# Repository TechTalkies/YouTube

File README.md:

# 🔧 Tech Talkies YouTube

This repository contains all the Arduino and electronics-related code from my YouTube videos. Each folder corresponds to a separate video or topic, with code examples, wiring tables, and useful documentation.

Support our open source projects:

## 📁 Folder Structure

Each subfolder is named after the video/project and includes:
- Arduino code (`.ino` files)
- Wiring diagrams or connection tables (in Markdown or image format)
- Supporting libraries or references (when applicable)
- A local `README.md` for project-specific details

## 📚 Topics Covered

Some of the topics you'll find here:
- DC motor control using L298N, TB6612FNG, and DRV8833
- Stepper motors with ULN2003 + 28BYJ-48
- Servo motor control with Arduino
- Sensor-based projects (IR, ultrasonic, etc.)
- ESP32 & Wi-Fi-based projects
- More being added regularly...

## 📺 Watch the Videos

Find the full tutorials on my [YouTube channel](https://www.youtube.com/@techtalkies1).

## 🌐 Visit the Website

For additional tutorials, updates, and resources, check out [techtalkies.in](https://techtalkies.in/)

## 🙌 Contribute or Contact

Suggestions or bug reports? Open an issue or drop a comment under the relevant YouTube video.

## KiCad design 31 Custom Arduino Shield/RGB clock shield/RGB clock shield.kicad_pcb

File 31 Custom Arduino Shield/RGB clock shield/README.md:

# Arduino-UNO-R4-Shield-Template
Arduino UNO R4 Shield Template for KiCad 6.<br/>
Based on official Arduino UNO R4 CAD.

## TO DO
- Make better 3D Headers to reflect real measurements.
## Schematic

## PCB View

## 3D View

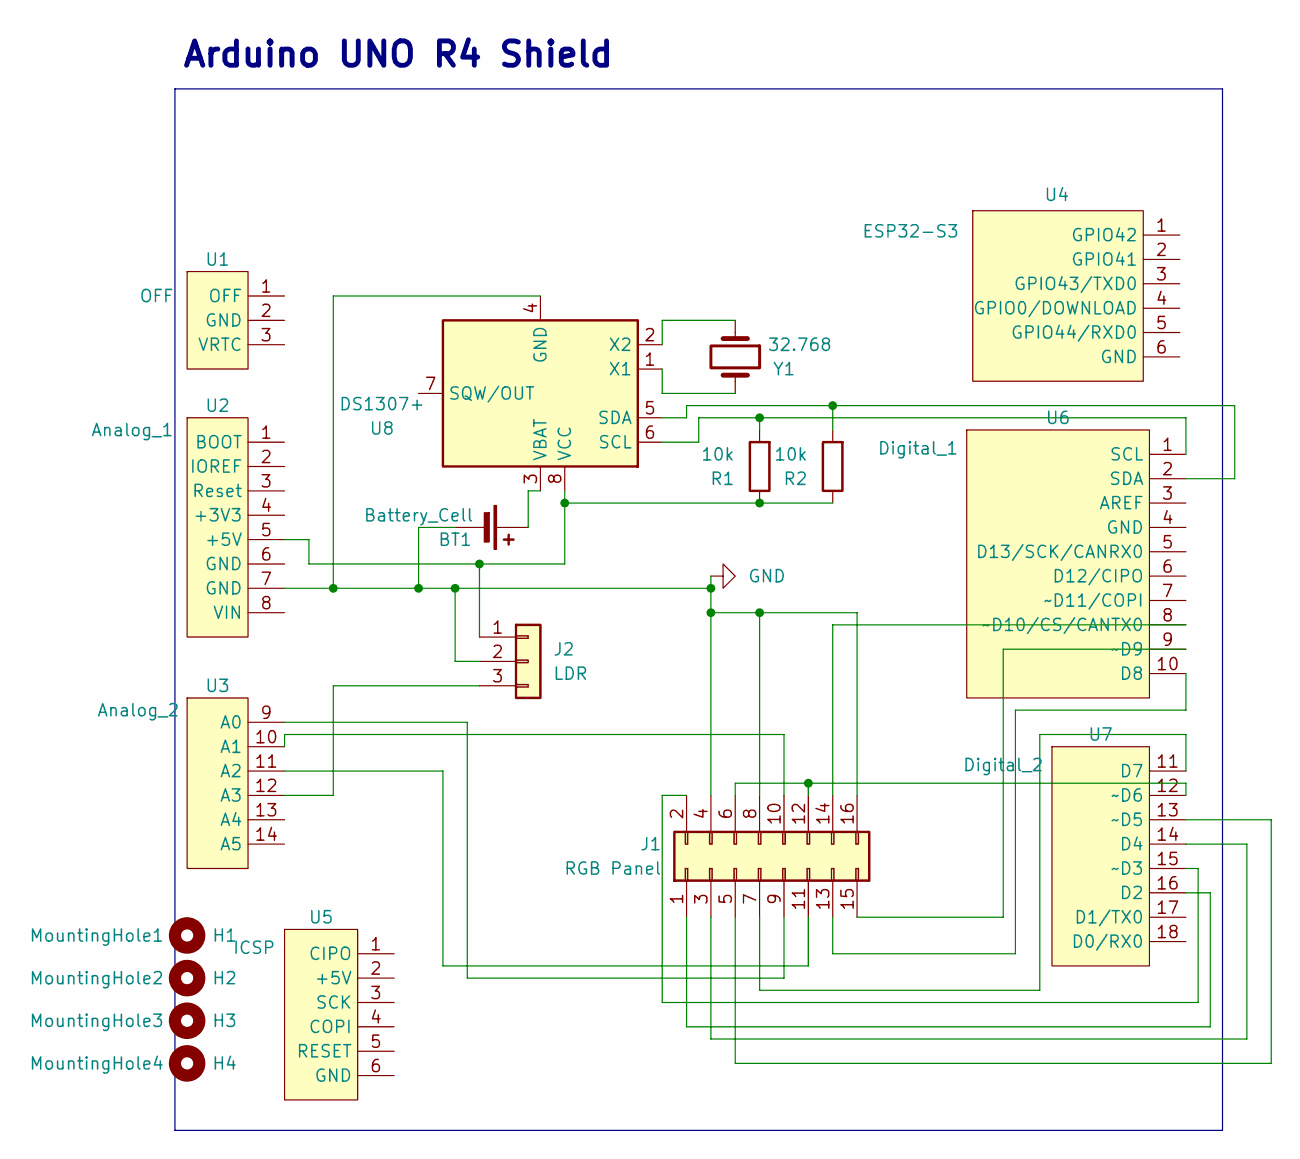
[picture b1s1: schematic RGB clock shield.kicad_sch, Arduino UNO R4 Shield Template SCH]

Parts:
BT1: Battery_Cell; BatteryHolder_Keystone_103_1x20mm
H1: MountingHole1; Arduino_MountingHole
H2: MountingHole2; Arduino_MountingHole
H3: MountingHole3; Arduino_MountingHole
H4: MountingHole4; Arduino_MountingHole
J1: RGB Panel; PinHeader_2x08_P2.54mm_Vertical
J2: LDR; PinHeader_1x03_P2.54mm_Vertical
R1, R2: 10k; R_1206_3216Metric_Pad1.30x1.75mm_HandSolder
U1: OFF; Arduino_PinSocket_1x03_P2.54mm_Vertical
U2: Analog_1; Arduino_PinSocket_1x08_P2.54mm_Vertical
U3: Analog_2; Arduino_PinSocket_1x06_P2.54mm_Vertical
U4: ESP32-S3; Arduino_PinSocket_2x03_P2.54mm_Vertical
U5: ICSP; Arduino_PinSocket_2x03_P2.54mm_Vertical
U6: Digital_1; Arduino_PinSocket_1x10_P2.54mm_Vertical
U7: Digital_2; Arduino_PinSocket_1x08_P2.54mm_Vertical
U8: DS1307+; DIP-8_W7.62mm
Y1: 32.768; Crystal_C38-LF_D3.0mm_L8.0mm_Vertical

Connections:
GND: BT1.2 (-), J1.4, J1.8, J1.16, J2.2, U2.7 (GND), U8.4 (GND)
unnamed: BT1.1 (+), U8.3 (VBAT)
unnamed: J1.2, U7.15 (~D3)
unnamed: J1.3, U7.14 (D4)
unnamed: J1.5, U7.13 (~D5)
unnamed: J1.7, U7.11 (D7)
unnamed: J1.9, U3.9 (A0)
unnamed: J1.10, U3.10 (A1)
unnamed: J1.11, U3.11 (A2)
unnamed: J1.6, J1.12, U7.12 (~D6)
unnamed: J1.13, U6.10 (D8)
unnamed: J1.14, U6.8 (~D10/CS/CANTX0)
unnamed: J1.15, U6.9 (~D9)
unnamed: J1.1 (R1), U7.16 (D2)
unnamed: J2.1, R1.1, R2.1, U2.5 (+5V), U8.8 (VCC)
unnamed: J2.3, U3.12 (A3)
unnamed: R1.2, U6.1 (SCL), U8.6 (SCL)
unnamed: R2.2, U6.2 (SDA), U8.5 (SDA)
unnamed: U8.1 (X1), Y1.2
unnamed: U8.2 (X2), Y1.1

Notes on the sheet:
Arduino UNO R4 Shield

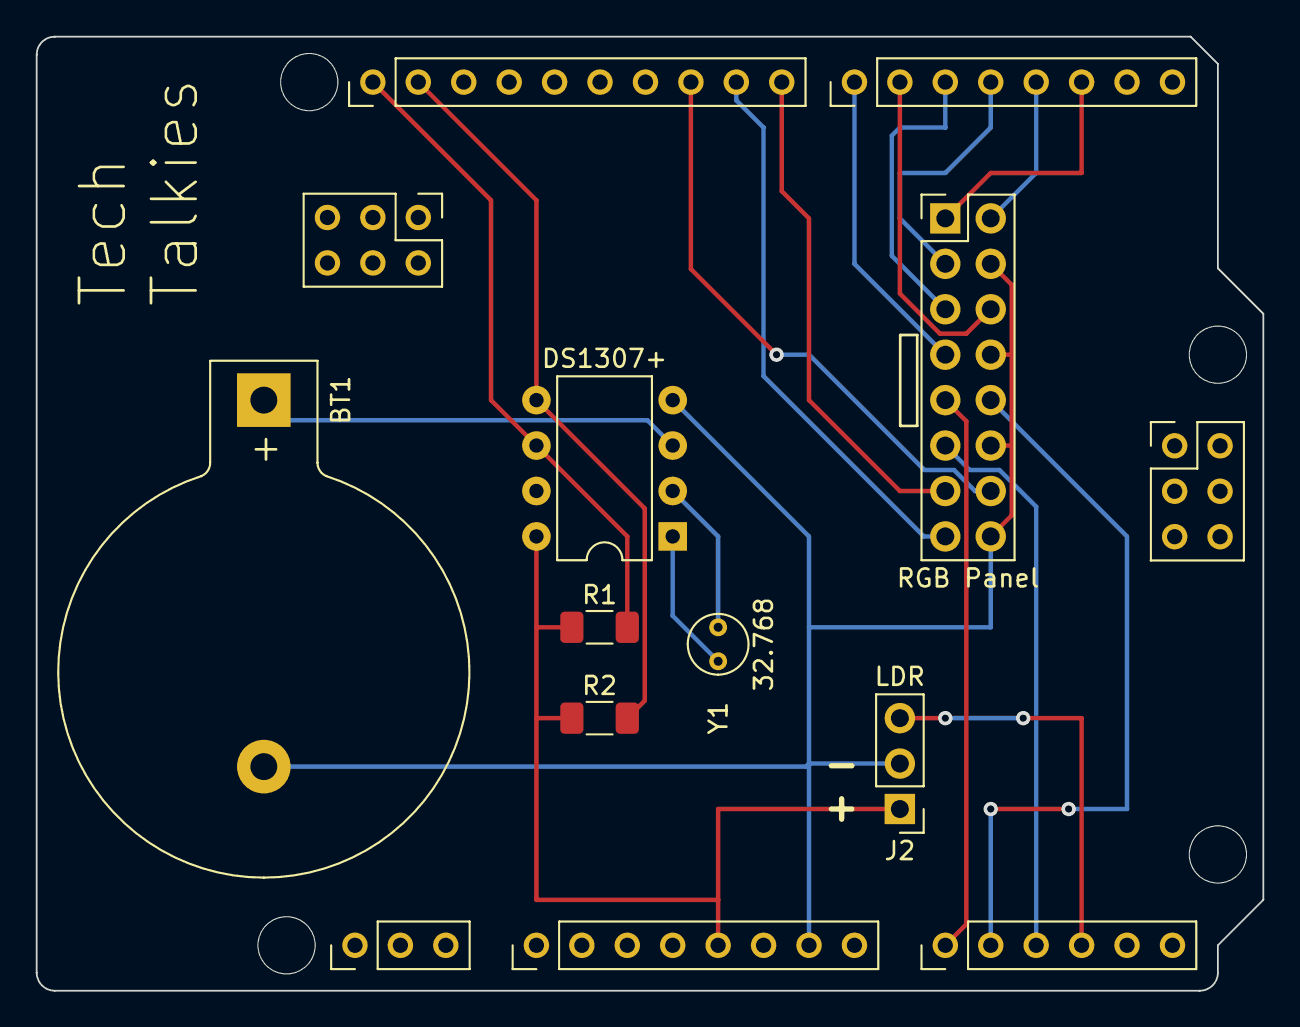
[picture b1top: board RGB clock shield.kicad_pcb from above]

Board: 2 copper layers, 68.6 x 53.3 mm, 18 parts (0 on the bottom side), 20 nets.

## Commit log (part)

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2025-11-23 Enhance Readme with project details and instructions
    Added detailed project information, features, components, wiring instructions, and button functions for the RF remote control project.
2025-12-20 Enhance Readme with project details and instructions
    Added detailed project description, features, hardware, software stack, voice commands, and instructions for running the voice-controlled robot arm project.
2026-01-03 Add initial implementation of UNIHIKER Shooter game
2026-04-17 Added screw details
2026-04-17 Ear screw sizes changed to take 2mm screws.
2026-05-11 Add lid 3D model for 2.9" e-ink displays
2026-05-12 2.9" Screen: - Remove 1mm from top opening in lid - Add EPD Cover for 2.9" screen
